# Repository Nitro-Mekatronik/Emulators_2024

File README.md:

# Emulators 2024

An open-source automotive diagnostic and emulation system with hardware and software components.

## Project Structure

### Firmware

#### STM32F103
- **BLE_K_Line_Analyzer**: Bluetooth Low Energy and K-Line protocol analysis software
- **Bootloader**: Custom bootloader for STM32F103
- **Emulators**: Emulator software for various vehicle protocols
- **Template**: Template for new firmware projects

### Hardware

#### Arduino_Emulator New
PCB designs and schematics for Arduino-based emulator hardware

#### Libraries
Component libraries used in hardware design

#### NTR-MAIN-U2xx
Main emulator board design

## Features

- STM32F103 microcontroller support
- Bluetooth Low Energy communication
- K-Line protocol support
- Arduino compatible design
- Custom bootloader
- Multi-protocol emulation

## Hardware Requirements

### STM32F103 Based Board
- STM32F103C8T6 or STM32F103CBT6 microcontroller
- 8MHz external crystal
- USB support
- Bluetooth module connection
- K-Line interface

### Arduino Emulator
- Arduino Nano or compatible board
- K-Line level converter
- Bluetooth module

## Software Requirements

### Firmware Development
- STM32CubeIDE 1.9.0 or higher
- STM32CubeMX
- ARM GCC Toolchain
- ST-Link software

### PCB Design
- KiCad 6.0 or higher
- Gerber viewer

## Installation

1. Clone the repository:
```bash
git clone https://github.com/Nitro-Mekatronik/Emulators_2024.git
```

2. For firmware development:
   - Install STM32CubeIDE
   - Open the project in IDE
   - Install required dependencies
   - Build the project

3. For hardware development:
   - Install KiCad
   - Open projects in Hardware folder
   - Generate Gerber files

## Usage

### Firmware Upload
1. Connect ST-Link programmer
2. Upload bootloader
3. Upload main firmware

### Emulator Usage
1. Connect hardware to vehicle OBD port
2. Connect via Bluetooth
3. Select appropriate protocol
4. Start emulation

## Contributing

Please read [CONTRIBUTING.md](CONTRIBUTING.md) for details on our code of conduct and the process for submitting pull requests.

## Security

If you discover any security-related issues, please email us instead of using the issue tracker.

## License

This project is licensed under the MIT License - see the [LICENSE](LICENSE) file for details.

## Support

For support, please create an issue in the GitHub issue tracker.

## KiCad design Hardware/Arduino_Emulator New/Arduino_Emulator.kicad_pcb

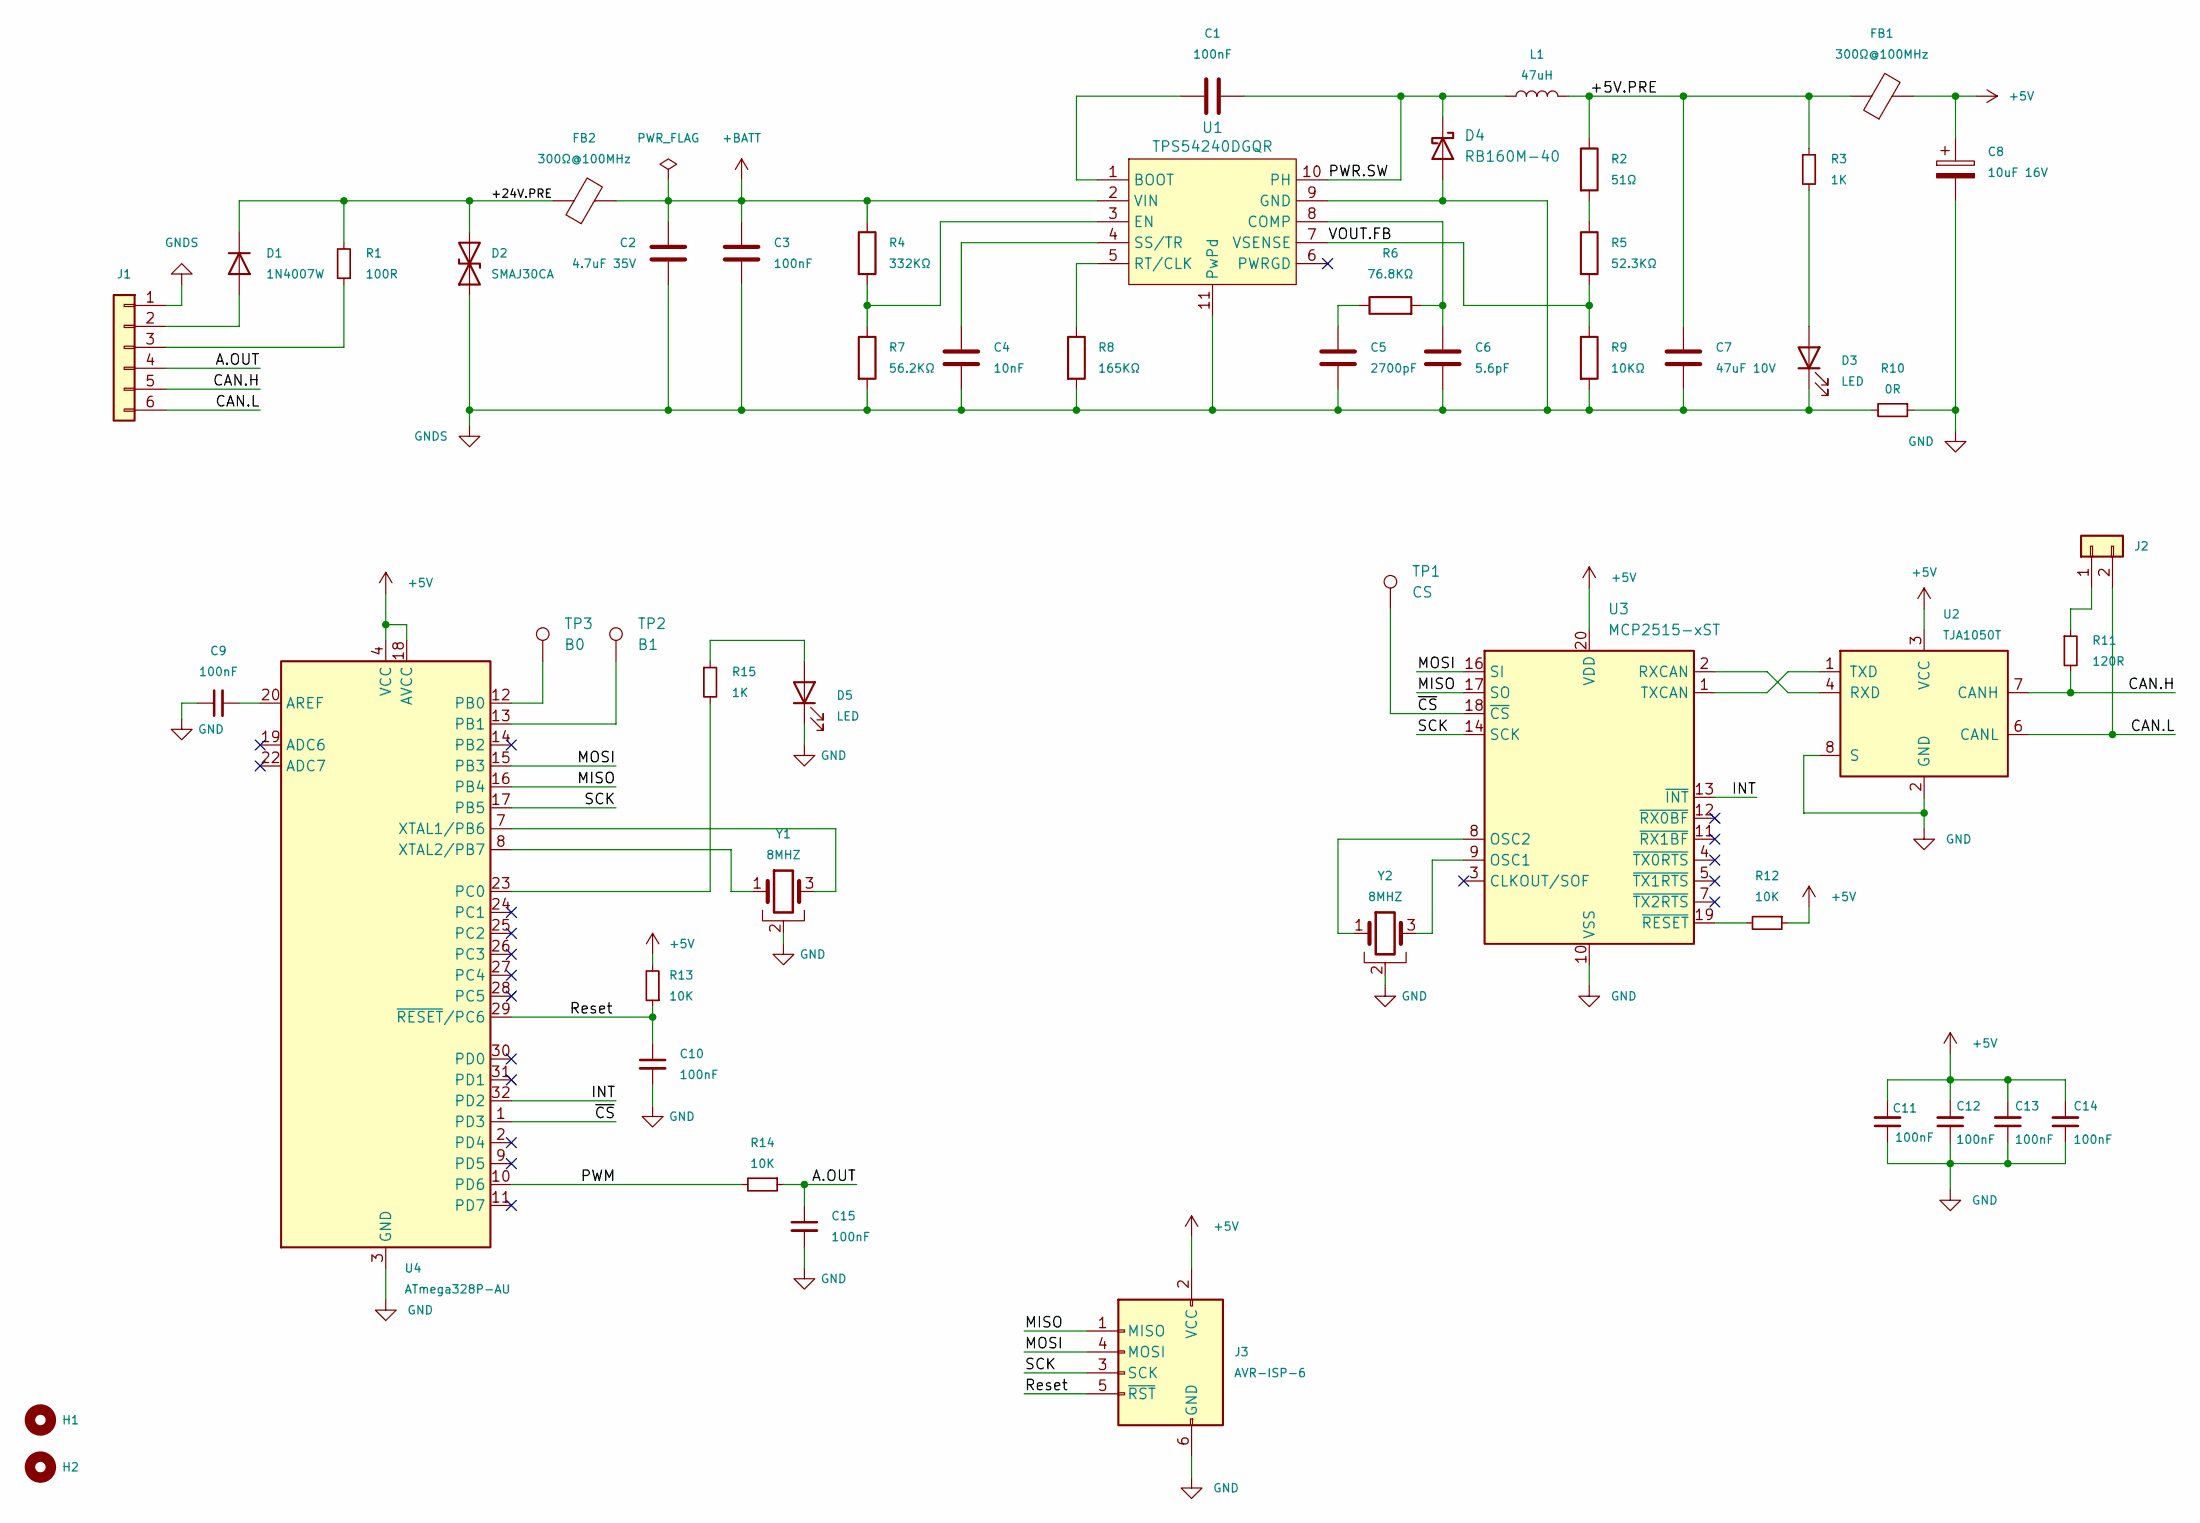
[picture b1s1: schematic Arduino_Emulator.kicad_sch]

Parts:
C1, C3, C9, C10, C11, C12, C13, C14, C15: 100nF; C_0402_1005Metric; LCSC C77020
C2: 4.7uF 35V; C_0603_1608Metric; LCSC C162274
C4: 10nF; C_0402_1005Metric; LCSC C386111
C5: 2700pF; C_0402_1005Metric; LCSC C162193
C6: 5.6pF; C_0402_1005Metric; LCSC C161155
C7: 47uF 10V; C_0805_2012Metric; LCSC C386058
C8: 10uF 16V; CP_EIA-3216-10_Kemet-I; LCSC C185772
D1: 1N4007W; D_SOD-123; LCSC C3018540
D2: SMAJ30CA; D_SMA; LCSC C356367
D3, D5: LED; LED_0402_1005Metric
D4: RB160M-40; D_SOD-123; LCSC C688896
FB1: 300Ω@100MHz; L_0805_2012Metric; LCSC C67451
FB2: 300Ω@100MHz; L_0603_1608Metric; LCSC C401489
H1, H2: MountingHole; MountingHole_2.5mm
J1: Conn_01x05; PinHeader_1x06_P2.54mm_Vertical
J2: Conn_01x02; SolderJumper-2_P1.3mm_Open_RoundedPad1.0x1.5mm
J3: AVR-ISP-6; PinHeader_2x03_P2.54mm_Vertical
L1: 47uH; L_Bourns-SRN4018; LCSC C341015
R1: 100R; R_0805_2012Metric; LCSC C17408
R2: 51Ω; R_0402_1005Metric; LCSC C325571
R3, R15: 1K; R_0402_1005Metric; LCSC C11702
R4: 332KΩ; R_0402_1005Metric; LCSC C321451
R5: 52.3KΩ; R_0402_1005Metric; LCSC C170333
R6: 76.8KΩ; R_0402_1005Metric; LCSC C158981
R7: 56.2KΩ; R_0402_1005Metric; LCSC C208917
R8: 165KΩ; R_0402_1005Metric; LCSC C25741
R9: 10KΩ; R_0402_1005Metric; LCSC C25854
R10: 0R; R_0402_1005Metric; LCSC C17168
R11: 120R; R_0805_2012Metric; LCSC C17437
R12, R13, R14: 10K; R_0402_1005Metric; LCSC C25744
TP1: CS; TestPoint_Pad_D1.5mm
TP2: B1; TestPoint_Pad_D1.5mm
TP3: B0; TestPoint_Pad_D1.5mm
U1: TPS54240DGQR; MSOP-10-1EP_3x3mm_P0.5mm_EP1.68x1.88mm; LCSC C53213
U2: TJA1050T; SOIC-8_3.9x4.9mm_P1.27mm; LCSC C6952
U3: MCP2515-xST; TSSOP-20_4.4x6.5mm_P0.65mm; LCSC C5250735
U4: ATmega328P-AU; TQFP-32_7x7mm_P0.8mm; LCSC C14877
Y1, Y2: 8MHZ; Resonator_SMD_muRata_CSTxExxV-3Pin_3.0x1.1mm; LCSC C22549

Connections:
+5V: C8.1, C11.2, C12.2, C13.2, C14.2, FB1.2, J3.2 (VCC), R12.1, R13.2, U2.3 (VCC), U3.20 (VDD), U4.4 (VCC), U4.6 (VCC), U4.18 (AVCC)
+BATT: C2.1, C3.1, FB2.2, R4.1, U1.2 (VIN)
/+5V.PRE: C7.1, FB1.1, L1.2, R2.1, R3.1
/+24V.PRE: D1.1 (K), D2.2 (A2), FB2.1, R1.2
/A.OUT: C15.1, J1.4, R14.1
/CAN.H: J1.5, R11.2, U2.7 (CANH)
/CAN.L: J1.6, J2.2, U2.6 (CANL)
/INT: U3.13 (~INT), U4.32 (PD2)
/MISO: J3.1 (MISO), U3.17 (SO), U4.16 (PB4)
/MOSI: J3.4 (MOSI), U3.16 (SI), U4.15 (PB3)
/PWM: R14.2, U4.10 (PD6)
/PWR.SW: C1.2, D4.1 (K), L1.1, U1.10 (PH)
/Reset: C10.1, J3.5 (~RST), R13.1, U4.29 (~RESET/PC6)
/SCK: J3.3 (SCK), U3.14 (SCK), U4.17 (PB5)
/VOUT.FB: R5.2, R9.1, U1.7 (VSENSE)
/~CS: TP1.1, U3.18 (~CS), U4.1 (PD3)
GND: C8.2, C9.1, C10.2, C11.1, C12.1, C13.1, C14.1, C15.2, D5.1 (K), J3.6 (GND), R10.1, U2.2 (GND), U2.8 (S), U3.10 (VSS), U4.3 (GND), U4.5 (GND), U4.21 (GND), Y1.2, Y2.2
GNDS: C2.2, C3.2, C4.1, C5.1, C6.1, C7.2, D2.1 (A1), D3.1 (K), D4.2 (A), J1.1, R7.2, R8.2, R9.2, R10.2, U1.9 (GND), U1.11 (PwPd)
unnamed: C5.2, R6.1
unnamed: D1.2 (A), J1.2
unnamed: D3.2 (A), R3.2
unnamed: D5.2 (A), R15.1
unnamed: J1.3, R1.1
unnamed: J2.1, R11.1
unnamed: R2.2, R5.1
unnamed: C1.1, U1.1 (BOOT)
unnamed: C6.2, R6.2, U1.8 (COMP)
unnamed: R4.2, R7.1, U1.3 (EN)
unnamed: R8.1, U1.5 (RT/CLK)
unnamed: C4.2, U1.4 (SS/TR)
unnamed: U2.4 (RXD), U3.2 (RXCAN)
unnamed: U2.1 (TXD), U3.1 (TXCAN)
unnamed: U3.9 (OSC1), Y2.3
unnamed: U3.8 (OSC2), Y2.1
unnamed: R12.2, U3.19 (~RESET)
unnamed: C9.2, U4.20 (AREF)
unnamed: TP3.1, U4.12 (PB0)
unnamed: TP2.1, U4.13 (PB1)
unnamed: U4.7 (XTAL1/PB6), Y1.3
unnamed: U4.8 (XTAL2/PB7), Y1.1

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
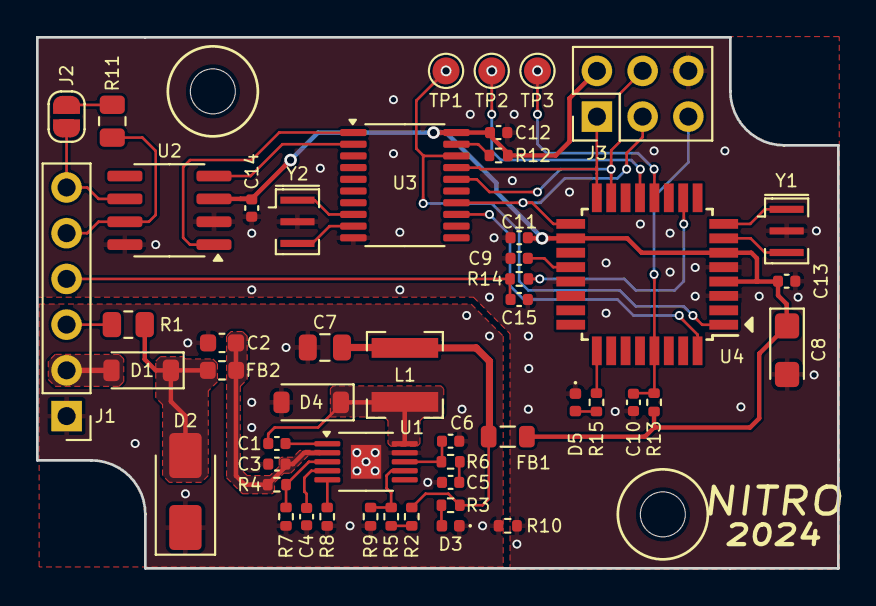
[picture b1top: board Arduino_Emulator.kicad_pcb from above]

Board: 2 copper layers, 44.5 x 29.5 mm, 52 parts (0 on the bottom side), 41 nets.

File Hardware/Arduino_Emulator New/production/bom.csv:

Designator,Footprint,Quantity,Value,LCSC Part #
"C1, C10, C11, C12, C13, C14, C15, C3, C9",0402,9,100nF,C77020
C2,0603,1,4.7uF 35V,C162274
C4,0402,1,10nF,C386111
C5,0402,1,2700pF,C162193
C6,0402,1,5.6pF,C161155
C7,0805,1,47uF 10V,C386058
C8,CP_EIA-3216-10_Kemet-I,1,10uF 16V,C185772
D1,D_SOD-123,1,1N4007W,C3018540
D2,D_SMA,1,SMAJ30CA,C356367
D3,0402,1,LED,C965790
D4,D_SOD-123,1,RB160M-40,C688896
D5,0402,1,LED,C434446
FB1,0805,1,300Ω@100MHz,C67451
FB2,0603,1,300Ω@100MHz,C401489
L1,L_Bourns-SRN4018,1,47uH,C341015
R1,0805,1,100R,C17408
R10,0402,1,0R,C17168
R11,0805,1,120R,C17437
"R12, R13, R14",0402,3,10K,C25744
"R15, R3",0402,2,1K,C11702
R2,0402,1,51Ω,C325571
R4,0402,1,332KΩ,C321451
R5,0402,1,52.3KΩ,C170333
R6,0402,1,76.8KΩ,C158981
R7,0402,1,56.2KΩ,C208917
R8,0402,1,165KΩ,C25741
R9,0402,1,10KΩ,C25854
U1,MSOP-10-1EP_3x3mm_P0.5mm_EP1.68x1.88mm,1,TPS54240DGQR,C53213
U2,SOIC-8_3.9x4.9mm_P1.27mm,1,TJA1050T,C6952
U3,TSSOP-20_4.4x6.5mm_P0.65mm,1,MCP2515-xST,C5250735
U4,TQFP-32_7x7mm_P0.8mm,1,ATmega328P-AU,C14877
"Y1, Y2",Resonator_SMD_muRata_CSTxExxV-3Pin_3.0x1.1mm,2,8MHZ,C22549

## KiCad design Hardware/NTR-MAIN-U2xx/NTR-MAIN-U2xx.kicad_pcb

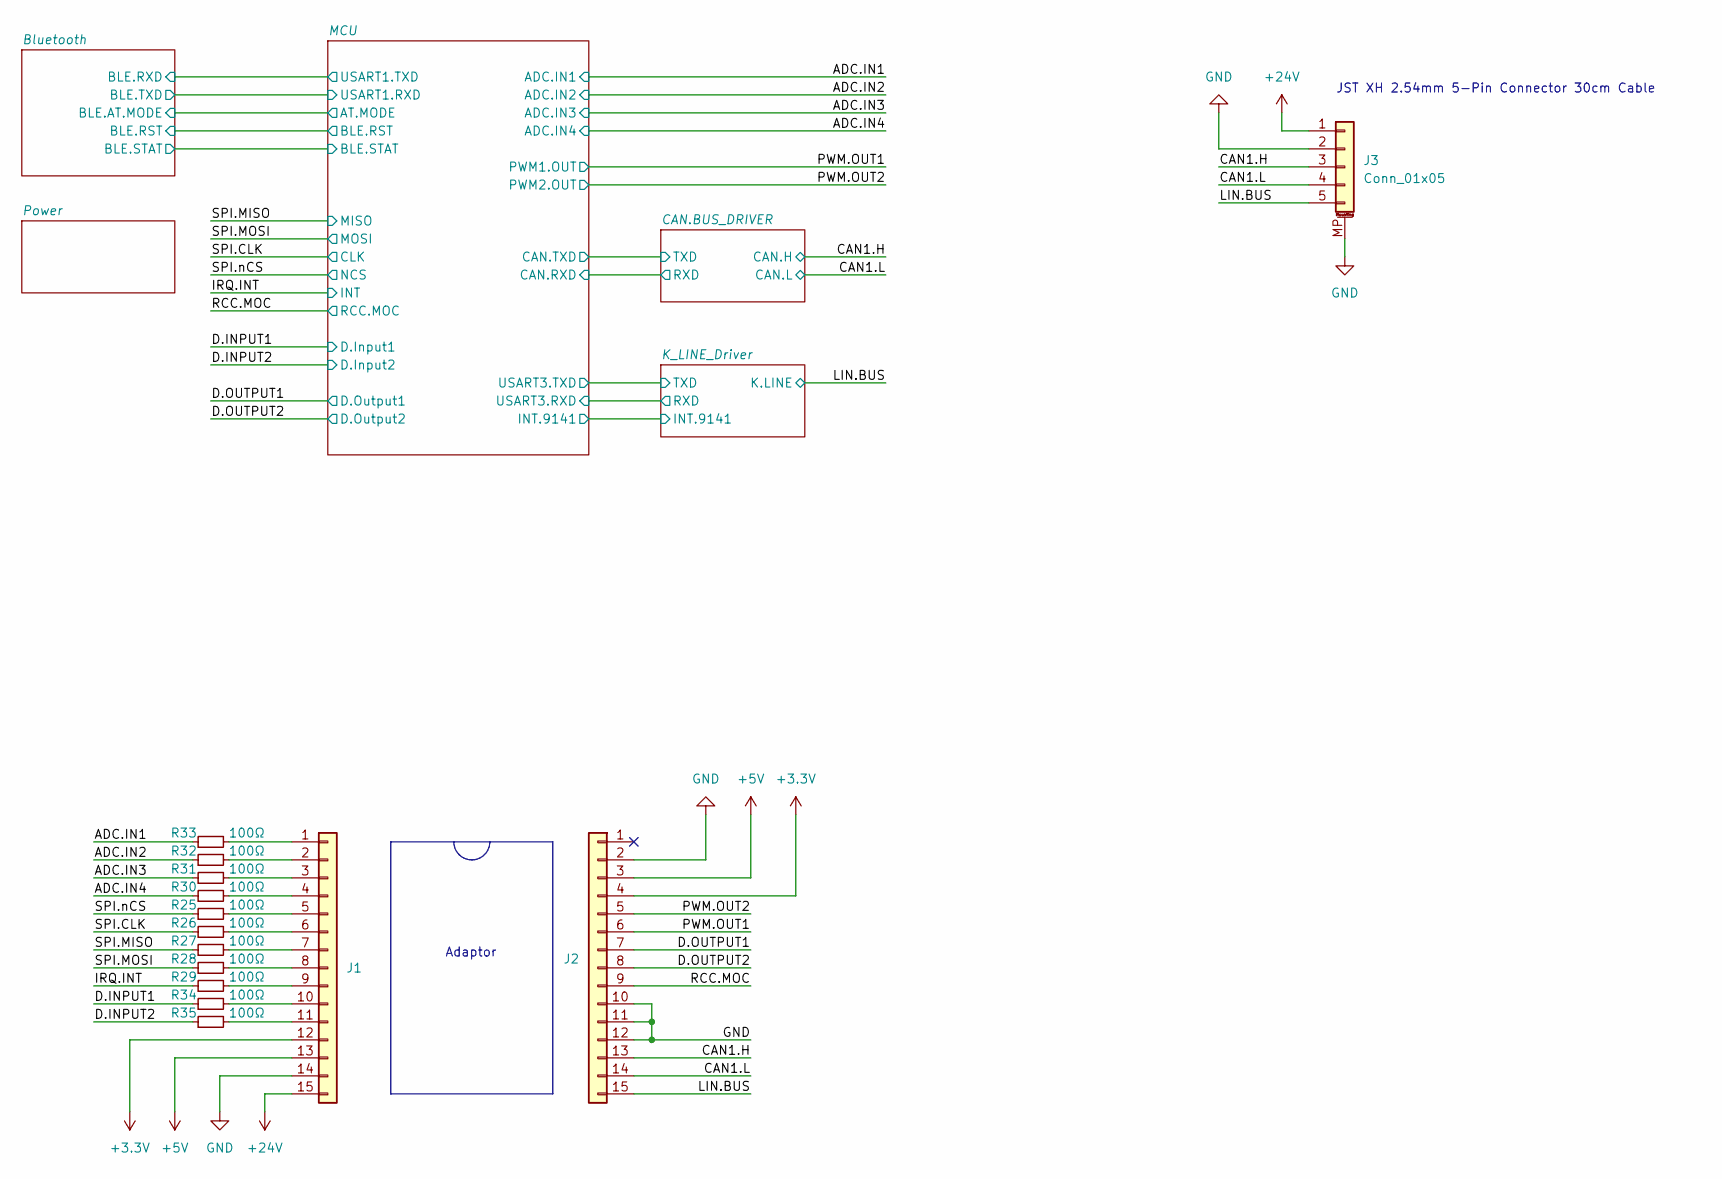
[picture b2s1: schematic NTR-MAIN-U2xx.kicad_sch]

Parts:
J1, J2: Conn_01x15; PinSocket_1x15_P2.54mm_Vertical; LCSC C2897378
J3: Conn_01x05; Molex_PicoBlade_53261-0571_1x05-1MP_P1.25mm_Horizontal; LCSC C481427
R25, R26, R27, R28, R29, R30, R31, R32, R33, R34, R35: 100Ω; R_0402_1005Metric; LCSC C25076

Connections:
+3.3V: J1.12, J2.4; also elsewhere on the board
+24V: J1.15, J3.1; also elsewhere on the board
/CAN1.H: J2.13, J3.3; also elsewhere on the board
/CAN1.L: J2.14, J3.4; also elsewhere on the board
/D.INPUT1: R34.1; also elsewhere on the board
/D.INPUT2: R35.1; also elsewhere on the board
/D.OUTPUT1: J2.7; also elsewhere on the board
/D.OUTPUT2: J2.8; also elsewhere on the board
/IRQ.INT: R29.1; also elsewhere on the board
/LIN.BUS: J2.15, J3.5; also elsewhere on the board
/PWM.OUT1: J2.6; also elsewhere on the board
/PWM.OUT2: J2.5; also elsewhere on the board
/RCC.MOC: J2.9; also elsewhere on the board
/SPI.CLK: R26.1; also elsewhere on the board
/SPI.MISO: R27.1; also elsewhere on the board
/SPI.MOSI: R28.1; also elsewhere on the board
/SPI.nCS: R25.1; also elsewhere on the board
unnamed: J1.1, R33.2
unnamed: J1.2, R32.2
unnamed: J1.3, R31.2
unnamed: J1.4, R30.2
unnamed: J1.5, R25.2
unnamed: J1.6, R26.2
unnamed: J1.7, R27.2
unnamed: J1.8, R28.2
unnamed: J1.9, R29.2
unnamed: J1.10, R34.2
unnamed: J1.11, R35.2

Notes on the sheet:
Adaptor
JST XH 2.54mm 5-Pin Connector 30cm Cable

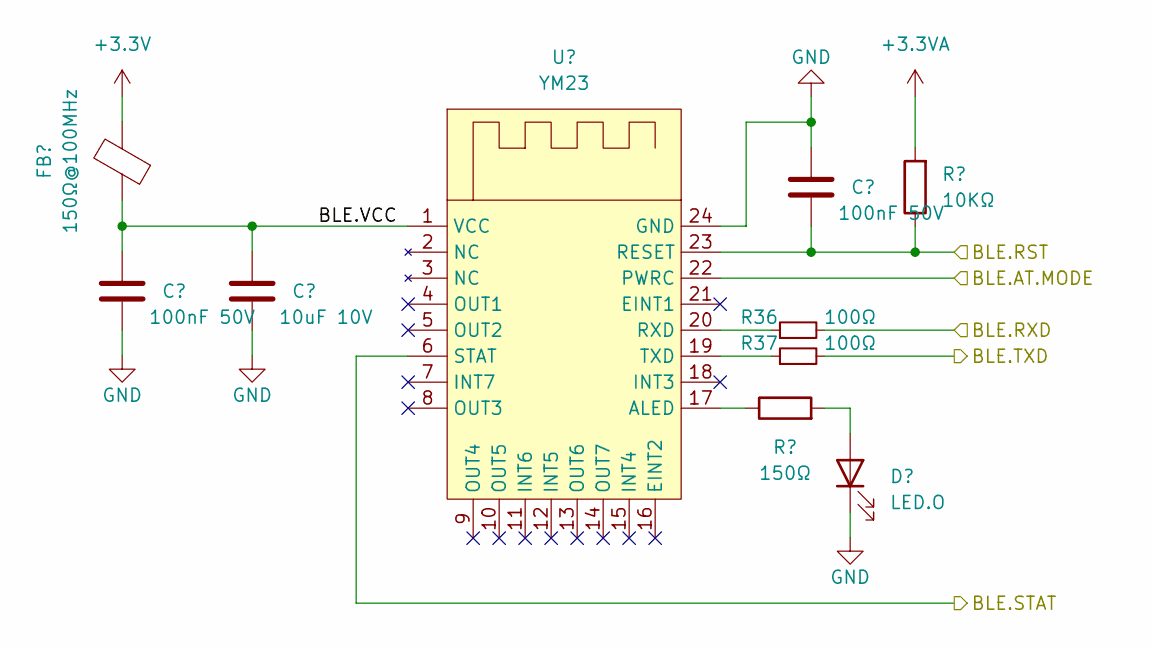
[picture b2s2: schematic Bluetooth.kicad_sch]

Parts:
C8, C10: 100nF 50V; C_0402_1005Metric; LCSC C77020
C9: 10uF 10V; C_0402_1005Metric; LCSC C315248
D4: LED.O; LED_0402_1005Metric; LCSC C434447
FB1: 150Ω@100MHz; L_0402_1005Metric; LCSC C160612
R15: 150Ω; R_0402_1005Metric; LCSC C25082
R16: 10KΩ; R_0402_1005Metric; LCSC C25744
R36, R37: 100Ω; R_0402_1005Metric; LCSC C25076
U4: YM23; JDY-08; LCSC C2905738

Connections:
+3.3V: FB1.2; also elsewhere on the board
/Bluetooth/BLE.AT.MODE: U4.22 (PWRC); also elsewhere on the board
/Bluetooth/BLE.RST: C10.2, R16.1, U4.23 (RESET); also elsewhere on the board
/Bluetooth/BLE.RXD: R36.2; also elsewhere on the board
/Bluetooth/BLE.STAT: U4.6 (STAT); also elsewhere on the board
/Bluetooth/BLE.TXD: R37.2; also elsewhere on the board
unnamed: D4.2 (A), R15.2
unnamed: R15.1, U4.17 (ALED)
unnamed: R36.1, U4.20 (RXD)
unnamed: R37.1, U4.19 (TXD)

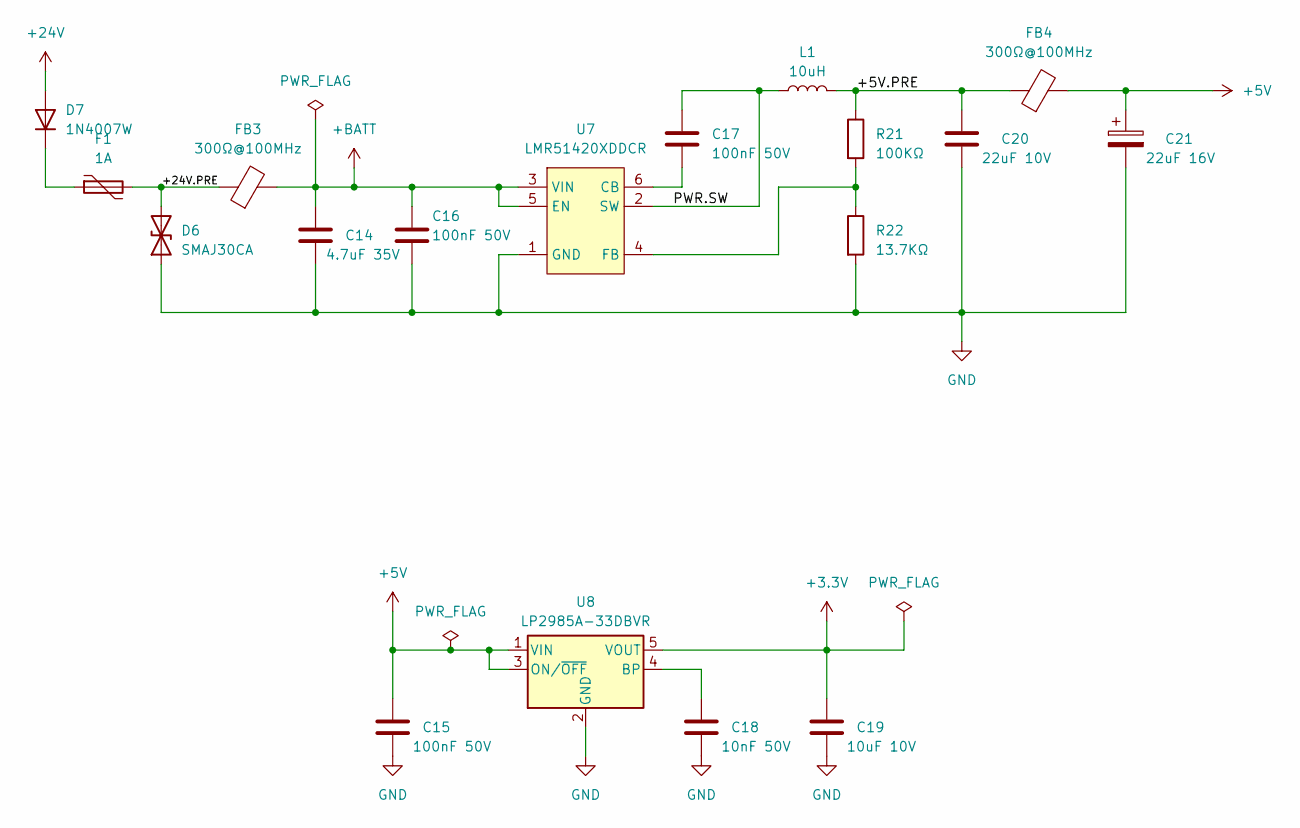
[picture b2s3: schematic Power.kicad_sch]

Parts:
C14: 4.7uF 35V; C_0603_1608Metric; LCSC C162274
C15, C16, C17: 100nF 50V; C_0402_1005Metric; LCSC C77020
C18: 10nF 50V; C_0402_1005Metric; LCSC C15195
C19: 10uF 10V; C_0402_1005Metric; LCSC C315248
C20: 22uF 10V; C_0805_2012Metric; LCSC C380336
C21: 22uF 16V; CP_EIA-3216-10_Kemet-I; LCSC C782264
D6: SMAJ30CA; D_SMA; LCSC C356367
D7: 1N4007W; D_SOD-123; LCSC C3018540
F1: 1A; Fuse_1812_4532Metric; LCSC C782762
FB3: 300Ω@100MHz; L_0603_1608Metric; LCSC C401489
FB4: 300Ω@100MHz; L_0805_2012Metric; LCSC C67451
L1: 10uH; L_Bourns-SRN4018; LCSC C135244
R21: 100KΩ; R_0402_1005Metric; LCSC C25741
R22: 13.7KΩ; R_0402_1005Metric; LCSC C25854
U7: LMR51420XDDCR; SOT-23-6; LCSC C5246146
U8: LP2985A-33DBVR; SOT-23-5; LCSC C89826

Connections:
+3.3V: C19.1, U8.5 (VOUT); also elsewhere on the board
+24V: D7.2 (A); also elsewhere on the board
+BATT: C14.1, C16.1, FB3.2, U7.3 (VIN), U7.5 (EN); also elsewhere on the board
/Power/+5V.PRE: C20.1, FB4.1, L1.2, R21.1
/Power/+24V.PRE: D6.2 (A2), F1.2, FB3.1
/Power/PWR.SW: C17.1, L1.1, U7.2 (SW)
unnamed: D7.1 (K), F1.1
unnamed: C17.2, U7.6 (CB)
unnamed: R21.2, R22.1, U7.4 (FB)

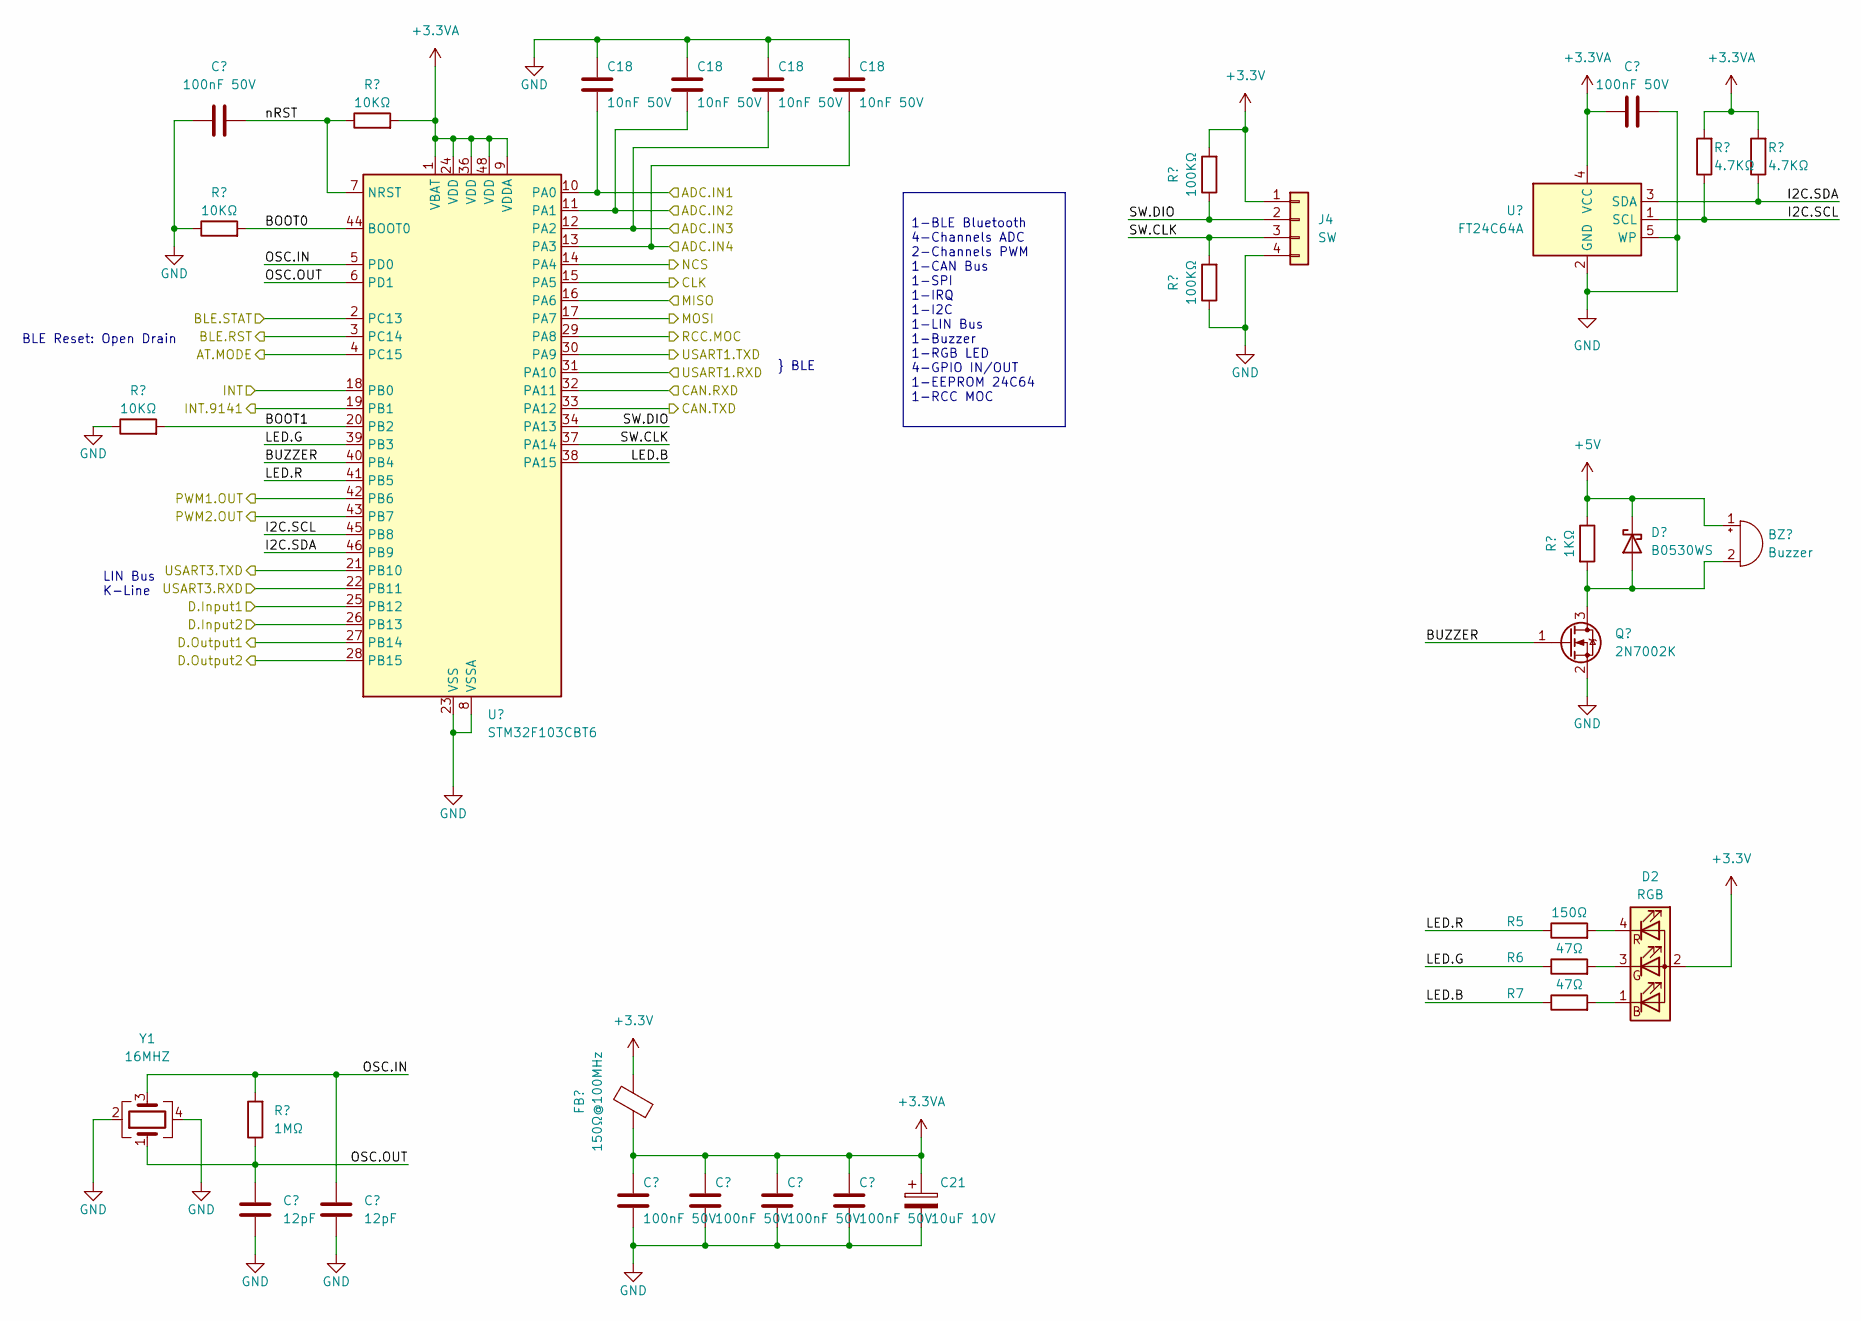
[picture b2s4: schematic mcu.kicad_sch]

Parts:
BZ1: Buzzer; MagneticBuzzer_CUI_CMT-8504-100-SMT; LCSC C255315
C1, C4, C22, C23, C24, C25: 100nF 50V; C_0402_1005Metric; LCSC C77020
C2, C3: 12pF; C_0402_1005Metric; LCSC C76948
C18: 10nF 50V; C_0402_1005Metric; LCSC C15195
C21: 10uF 10V; CP_EIA-3216-10_Kemet-I; LCSC C7177
D1: B0530WS; D_SOD-323; LCSC C2961213
D2: RGB; LED_Cree-PLCC4_2x2mm_CW; LCSC C375569
FB1: 150Ω@100MHz; L_0402_1005Metric; LCSC C160612
J4: SW; PinHeader_1x04_P2.54mm_Vertical
Q1: 2N7002K; SOT-23; LCSC C2848187
R1, R2, R4: 10KΩ; R_0402_1005Metric; LCSC C25744
R3: 1MΩ; R_0402_1005Metric; LCSC C138033
R5: 150Ω; R_0402_1005Metric; LCSC C25082
R6, R7: 47Ω; R_0402_1005Metric; LCSC C25168
R8: 1KΩ; R_0402_1005Metric; LCSC C11702
R9, R10: 4.7KΩ; R_0402_1005Metric; LCSC C25900
R23, R24: 100KΩ; R_0402_1005Metric; LCSC C25741
U1: STM32F103CBT6; LQFP-48_7x7mm_P0.5mm; LCSC C8304
U2: FT24C64A; SOT-23-5; LCSC C5263778
Y1: 16MHZ; Crystal_SMD_2520-4Pin_2.5x2.0mm; LCSC C13738

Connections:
+3.3V: D2.2 (A), FB1.2, J4.1, R23.2; also elsewhere on the board
/Bluetooth/BLE.AT.MODE: U1.4 (PC15); also elsewhere on the board
/Bluetooth/BLE.RST: U1.3 (PC14); also elsewhere on the board
/Bluetooth/BLE.RXD: U1.30 (PA9); also elsewhere on the board
/Bluetooth/BLE.STAT: U1.2 (PC13); also elsewhere on the board
/Bluetooth/BLE.TXD: U1.31 (PA10); also elsewhere on the board
/CAN.BUS_DRIVER/RXD: U1.32 (PA11); also elsewhere on the board
/CAN.BUS_DRIVER/TXD: U1.33 (PA12); also elsewhere on the board
/D.INPUT1: U1.25 (PB12); also elsewhere on the board
/D.INPUT2: U1.26 (PB13); also elsewhere on the board
/D.OUTPUT1: U1.27 (PB14); also elsewhere on the board
/D.OUTPUT2: U1.28 (PB15); also elsewhere on the board
/IRQ.INT: U1.18 (PB0); also elsewhere on the board
/K_LINE_Driver/INT.9141: U1.19 (PB1); also elsewhere on the board
/K_LINE_Driver/RXD: U1.22 (PB11); also elsewhere on the board
/K_LINE_Driver/TXD: U1.21 (PB10); also elsewhere on the board
/MCU/BOOT0: R2.2, U1.44 (BOOT0)
/MCU/BOOT1: R1.2, U1.20 (PB2)
/MCU/BUZZER: Q1.1 (G), U1.40 (PB4)
/MCU/I2C.SCL: R9.1, U1.45 (PB8), U2.1 (SCL)
/MCU/I2C.SDA: R10.1, U1.46 (PB9), U2.3 (SDA)
/MCU/LED.B: R7.1, U1.38 (PA15)
/MCU/LED.G: R6.1, U1.39 (PB3)
/MCU/LED.R: R5.1, U1.41 (PB5)
/MCU/OSC.IN: C3.1, R3.2, U1.5 (PD0), Y1.3
/MCU/OSC.OUT: C2.1, R3.1, U1.6 (PD1), Y1.1
/MCU/SW.CLK: J4.3, R24.2, U1.37 (PA14)
/MCU/SW.DIO: J4.2, R23.1, U1.34 (PA13)
/MCU/nRST: C1.2, R4.1, U1.7 (NRST)
/PWM.OUT1: U1.42 (PB6); also elsewhere on the board
/PWM.OUT2: U1.43 (PB7); also elsewhere on the board
/RCC.MOC: U1.29 (PA8); also elsewhere on the board
/SPI.CLK: U1.15 (PA5); also elsewhere on the board
/SPI.MISO: U1.16 (PA6); also elsewhere on the board
/SPI.MOSI: U1.17 (PA7); also elsewhere on the board
/SPI.nCS: U1.14 (PA4); also elsewhere on the board
unnamed: BZ1.2 (+), D1.2 (A), Q1.3 (D), R8.2
unnamed: D2.1 (BK), R7.2
unnamed: D2.3 (GK), R6.2
unnamed: D2.4 (RK), R5.2

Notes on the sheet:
1-BLE Bluetooth 4-Channels ADC 2-Channels PWM 1-CAN Bus 1-SPI 1-IRQ 1-I2C 1-LIN Bus 1-Buzzer 1-RGB LED 4-GPIO IN/OUT 1-EEPROM 24C64 1-RCC MOC
LIN Bus K-Line
BLE Reset: Open Drain
} BLE

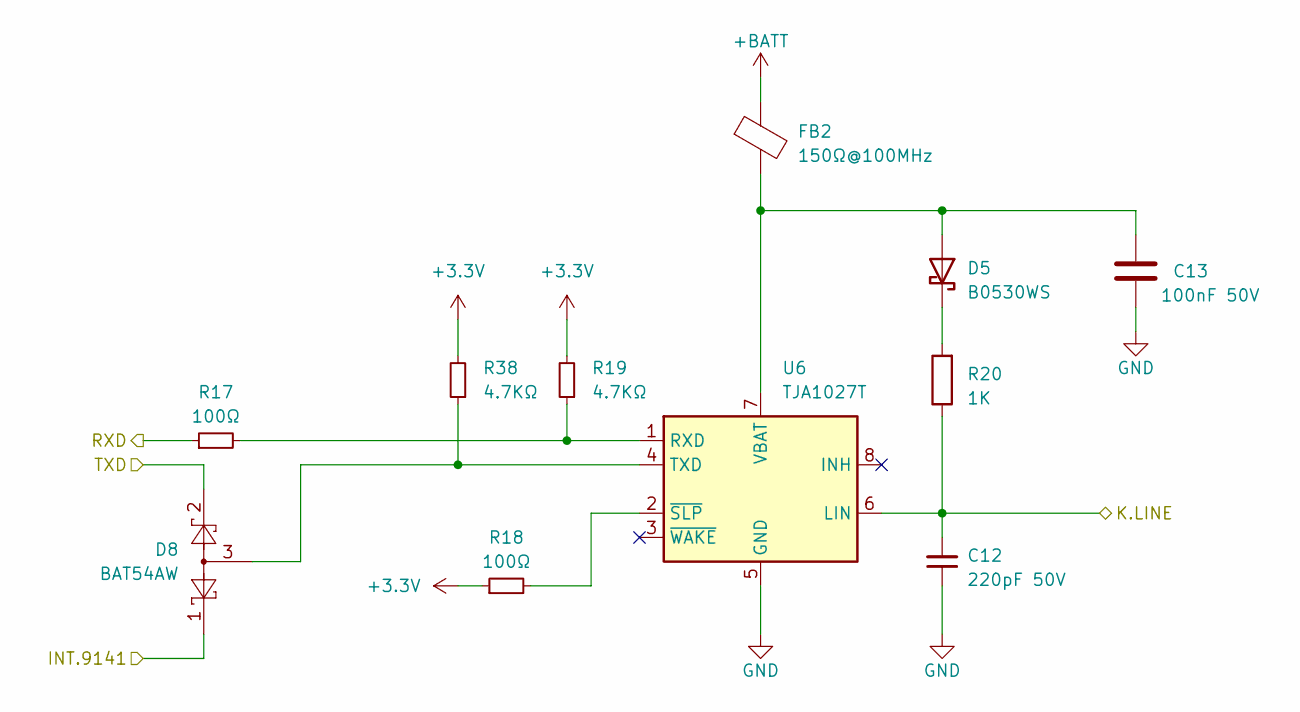
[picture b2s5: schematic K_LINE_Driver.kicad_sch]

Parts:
C12: 220pF 50V; C_0402_1005Metric; LCSC C107025
C13: 100nF 50V; C_0402_1005Metric; LCSC C77020
D5: B0530WS; D_SOD-323; LCSC C2961213
D8: BAT54AW; SOT-323_SC-70; LCSC C890244
FB2: 150Ω@100MHz; L_0402_1005Metric; LCSC C160612
R17, R18: 100Ω; R_0402_1005Metric; LCSC C25076
R19, R38: 4.7KΩ; R_0402_1005Metric; LCSC C25900
R20: 1K; R_0603_1608Metric; LCSC C21190
U6: TJA1027T; SO-8_3.9x4.9mm_P1.27mm; LCSC C194371

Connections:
+3.3V: R18.1, R19.2, R38.2; also elsewhere on the board
+BATT: FB2.1; also elsewhere on the board
/K_LINE_Driver/INT.9141: D8.1; also elsewhere on the board
/K_LINE_Driver/RXD: R17.1; also elsewhere on the board
/K_LINE_Driver/TXD: D8.2; also elsewhere on the board
/LIN.BUS: C12.2, R20.1, U6.6 (LIN); also elsewhere on the board
unnamed: C13.1, D5.2 (A), FB2.2, U6.7 (VBAT)
unnamed: D5.1 (K), R20.2
unnamed: R17.2, R19.1, U6.1 (RXD)
unnamed: D8.3, R38.1, U6.4 (TXD)
unnamed: R18.2, U6.2 (~SLP)

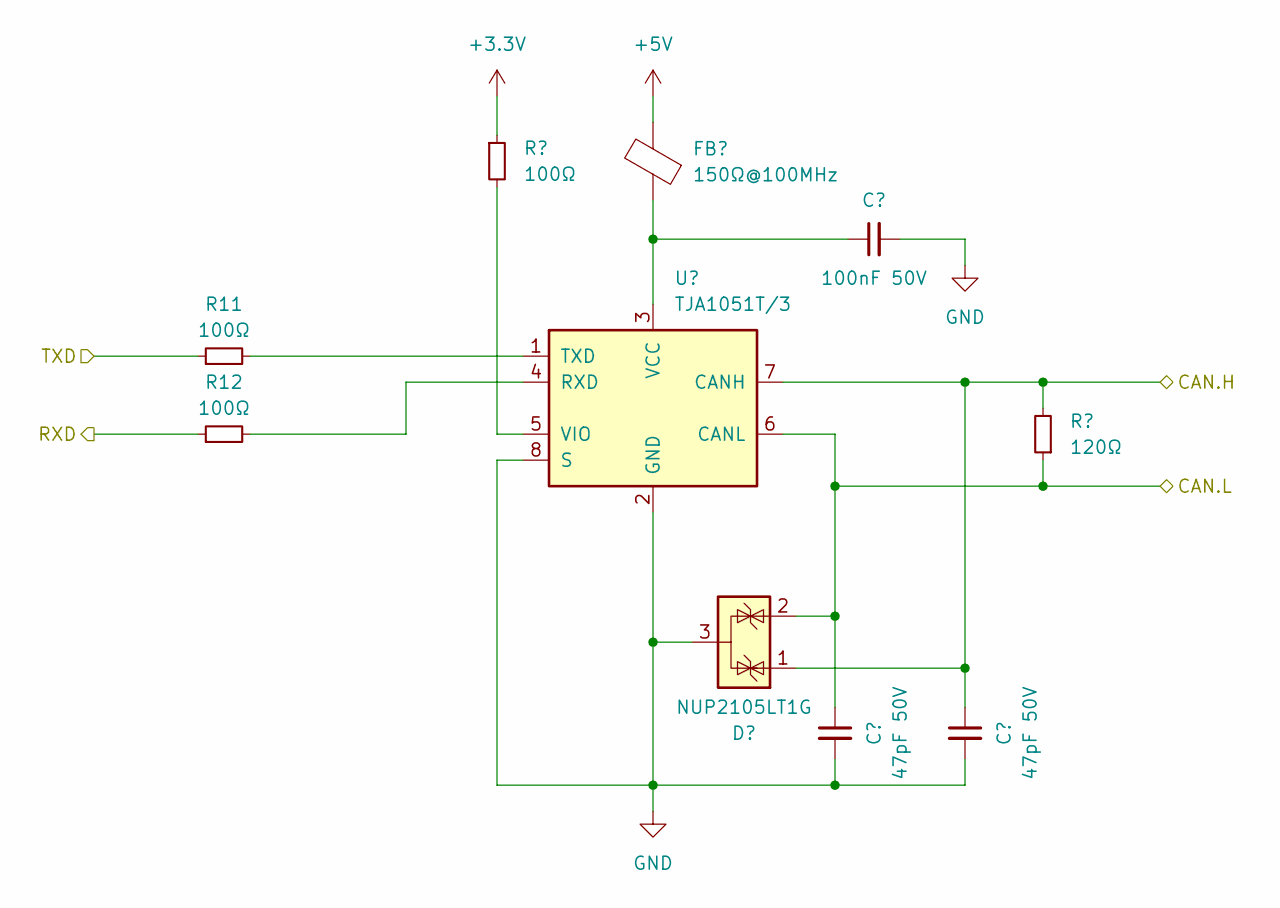
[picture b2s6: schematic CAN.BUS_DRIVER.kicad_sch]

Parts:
C5: 100nF 50V; C_0402_1005Metric; LCSC C77020
C6, C7: 47pF 50V; C_0402_1005Metric; LCSC C76970
D3: NUP2105LT1G; SOT-23; LCSC C2890118
FB6: 150Ω@100MHz; L_0402_1005Metric; LCSC C160612
R11, R12, R13: 100Ω; R_0402_1005Metric; LCSC C25076
R14: 120Ω; R_0805_2012Metric; LCSC C17437
U3: TJA1051T/3; SOIC-8_3.9x4.9mm_P1.27mm; LCSC C5342108

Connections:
+3.3V: R13.1; also elsewhere on the board
/CAN1.H: C7.1, D3.1 (K), R14.2, U3.7 (CANH); also elsewhere on the board
/CAN1.L: C6.1, D3.2 (K), R14.1, U3.6 (CANL); also elsewhere on the board
/CAN.BUS_DRIVER/RXD: R12.1; also elsewhere on the board
/CAN.BUS_DRIVER/TXD: R11.1; also elsewhere on the board
unnamed: R12.2, U3.4 (RXD)
unnamed: R11.2, U3.1 (TXD)
unnamed: C5.1, FB6.1, U3.3 (VCC)
unnamed: R13.2, U3.5 (VIO)

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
